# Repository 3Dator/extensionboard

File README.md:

3Dator extensionboard firmware
======

This repository contains the firmware for our tiny extensionboard that is used to drive the LEDs and both Fans.

Also there is a voltage devider for the 12V Feedback pin of the inductive z probe.

For more information visit our website or wiki:

http://3dator.com

http://wiki.3dator.com

#how to use
If you want to play arrount with the sourcecode on your board you need a ISP Programmer which is supported by Arduino IDE. (e.g. stk 500)

#License
Please note that the material in this repository is licensed with the CC BY-NC-SA

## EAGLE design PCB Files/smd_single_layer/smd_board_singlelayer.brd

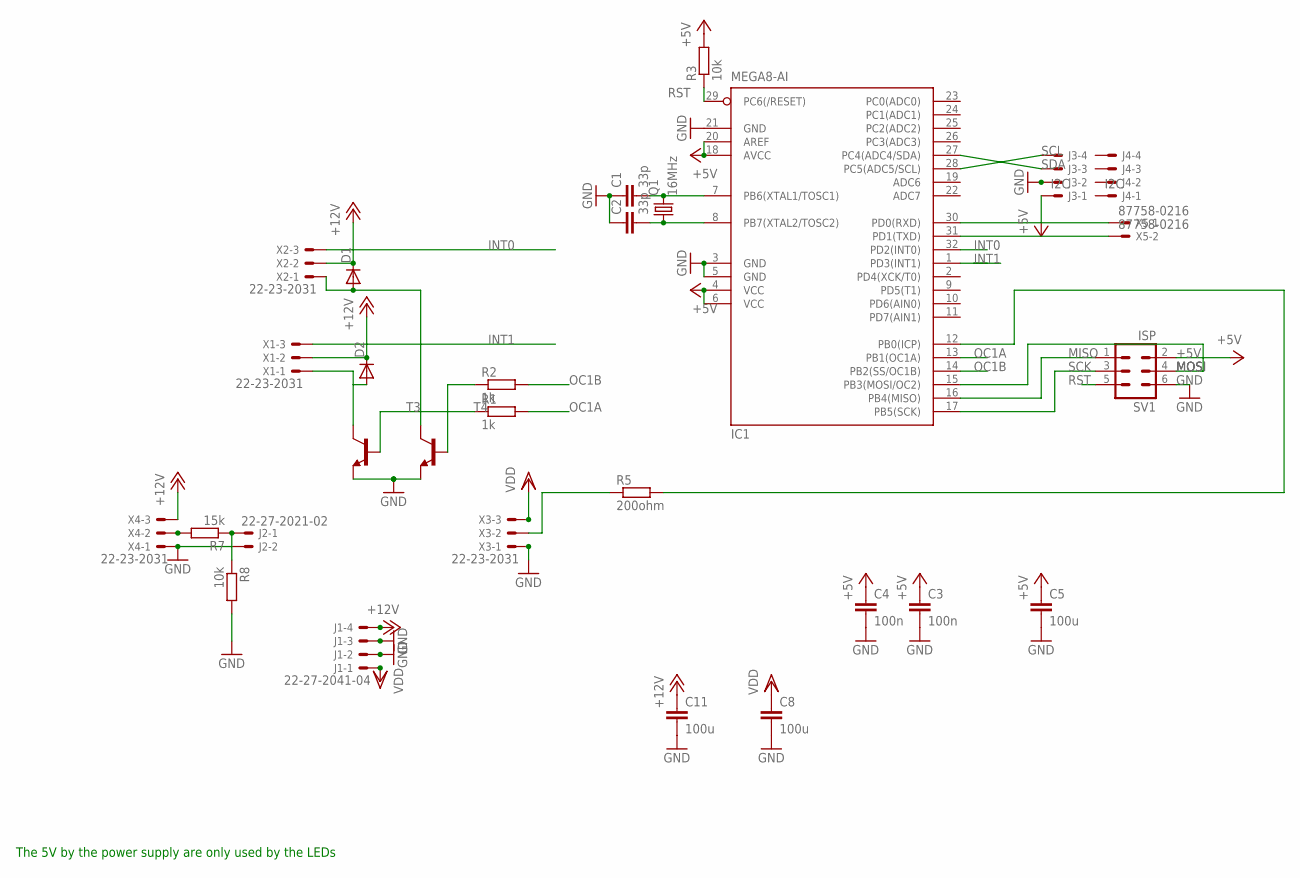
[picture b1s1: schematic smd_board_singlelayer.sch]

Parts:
C1, C2: 33p; C1206
C3, C4: 100n; C1206
C5, C8, C11: 100u; C1206
D1, D2: DIODE-SOD80C; SOD80C
IC1: MEGA8-AI; TQFP32-08
J1: 22-27-2041-04; 6410-04
J2: 22-27-2021-02; 6410-02
J3, J4: I2C; 6410-04
Q1: 16MHz; HC49UP
R1, R2: 1k; M1206
R3, R8: 10k; M1206
R5: 200ohm; M1206
R7: 15k; M1206
SV1: ISP; ML6
T3, T4: BC808-NPN-SOT23-BEC; SOT23-BEC
X1, X2, X3, X4: 22-23-2031
X5: 87758-0216

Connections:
+5V: C3.1, C4.1, C5.1, IC1.4 (VCC), IC1.6 (VCC), IC1.18 (AVCC), IC1.20 (AREF), J3.1, R3.2, SV1.2
+12V: C11.1, D1.C, D2.C, J1.4, X1.2, X2.2, X4.3
GND: C1.1, C2.1, C3.2, C4.2, C5.2, C8.2, C11.2, IC1.3 (GND), IC1.5 (GND), IC1.21 (GND), J1.2, J1.3, J2.2, J3.2, R8.2, SV1.6, T3.E, T4.E, X3.1, X4.1
INT0: IC1.32 (PD2(INT0)), X2.3
INT1: IC1.1 (PD3(INT1)), X1.3
MISO: IC1.16 (PB4(MISO)), SV1.1
MOSI: IC1.15 (PB3(MOSI/OC2)), SV1.4
unnamed: C1.2, IC1.7 (PB6(XTAL1/TOSC1)), Q1.2
unnamed: D2.A, T3.C, X1.1
unnamed: D1.A, T4.C, X2.1
unnamed: R2.1, T4.B
unnamed: R1.1, T3.B
unnamed: R5.1, X3.2
unnamed: C2.2, IC1.8 (PB7(XTAL2/TOSC2)), Q1.1
unnamed: IC1.30 (PD0(RXD)), X5.1
unnamed: R7.2, X4.2
unnamed: J2.1, R7.1, R8.1
unnamed: IC1.12 (PB0(ICP)), R5.2
unnamed: IC1.31 (PD1(TXD)), X5.2
OC1A: IC1.13 (PB1(OC1A)), R1.2
OC1B: IC1.14 (PB2(SS/OC1B)), R2.2
RST: IC1.29 (PC6(/RESET)), R3.1, SV1.5
SCK: IC1.17 (PB5(SCK)), SV1.3
SCL: IC1.28 (PC5(ADC5/SCL)), J3.4
SDA: IC1.27 (PC4(ADC4/SDA)), J3.3
VDD: C8.1, J1.1, X3.3

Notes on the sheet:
The 5V by the power supply are only used by the LEDs

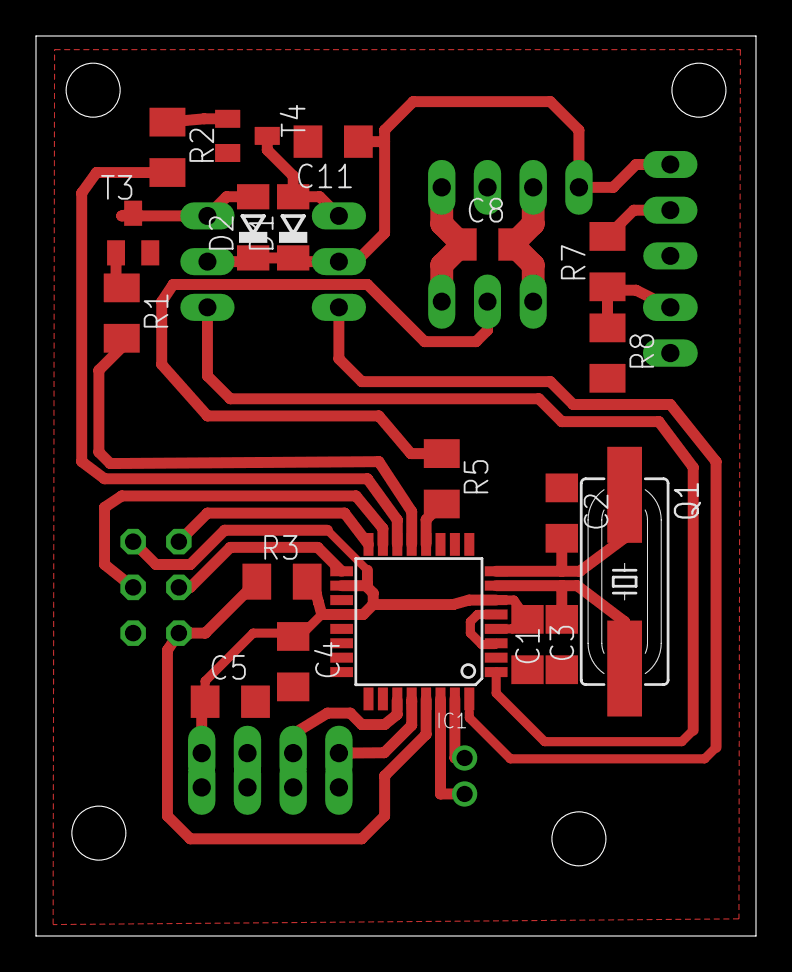
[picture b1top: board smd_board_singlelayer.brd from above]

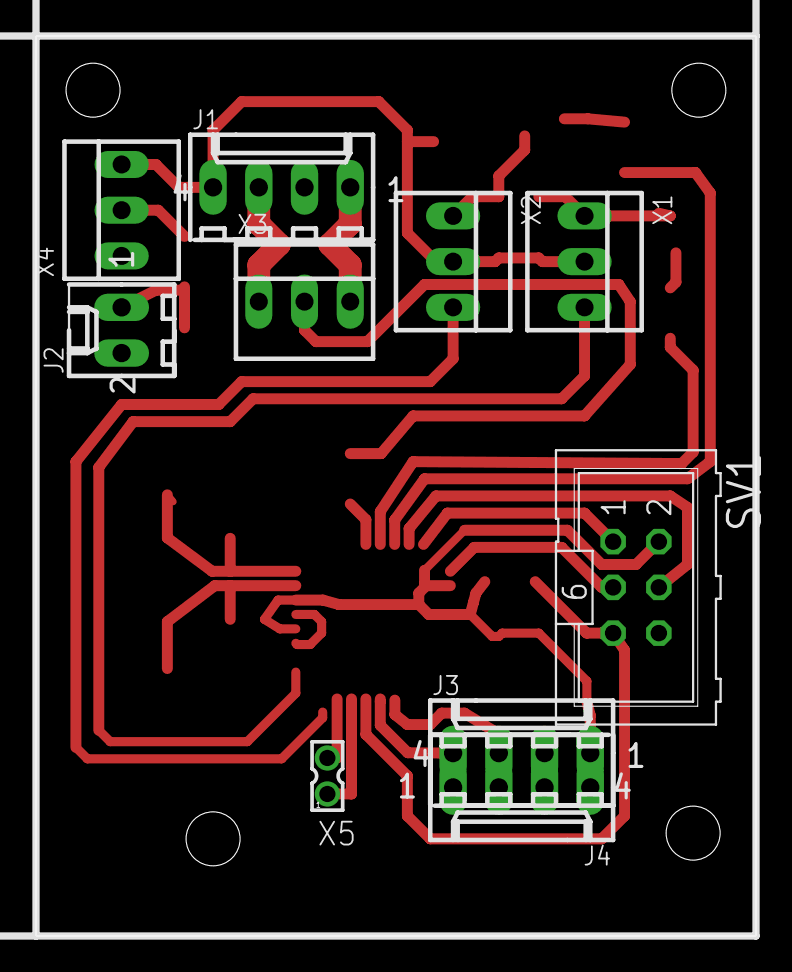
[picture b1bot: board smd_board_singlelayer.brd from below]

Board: 2 copper layers, 40.0 x 50.0 mm, 29 parts (10 on the bottom side), 26 nets.

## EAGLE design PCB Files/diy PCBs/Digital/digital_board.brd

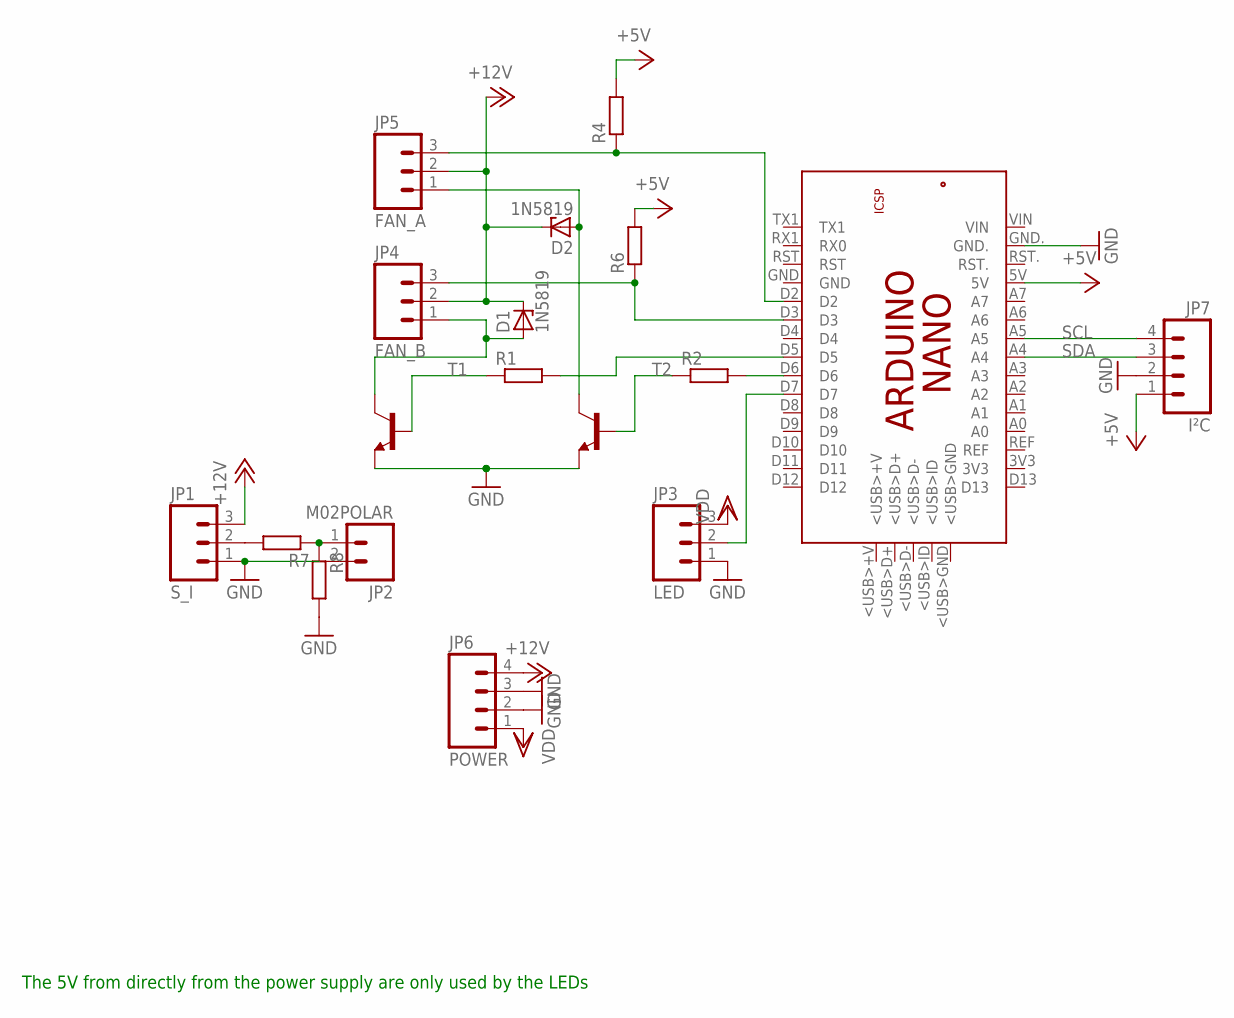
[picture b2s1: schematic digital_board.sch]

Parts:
D1, D2: 1N5819; DO35Z10
JP1: S_I; MOLEX-1X3
JP2: M02POLAR; MOLEX-1X2
JP3: LED; MOLEX-1X3
JP4: FAN_B; MOLEX-1X3
JP5: FAN_A; MOLEX-1X3
JP6: POWER; MOLEX-1X4
JP7: I²C; MOLEX-1X4
PCB2: ARDUINO_NANO
R1, R2, R4, R6, R7, R8: R-EU_0309/10; 0309/10
T1, T2: BC548-NPN-TO92-CBE; TO92-CBE

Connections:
+5V: JP7.1, PCB2.5V, R4.2, R6.2
+12V: D1.C, D2.C, JP1.3, JP4.2, JP5.2, JP6.4
GND: JP1.1, JP2.2, JP3.1, JP6.2, JP6.3, JP7.2, PCB2.GND., R8.2, T1.E, T2.E
unnamed: D1.A, JP4.1, T1.C
unnamed: D2.A, JP5.1, T2.C
unnamed: R1.1, T1.B
unnamed: PCB2.D5, R1.2
unnamed: PCB2.D6, R2.2
unnamed: JP4.3, PCB2.D3, R6.1
unnamed: JP5.3, PCB2.D2, R4.1
unnamed: JP1.2, R7.2
unnamed: JP2.1, R7.1, R8.1
unnamed: JP3.2, PCB2.D7
SCL: JP7.4, PCB2.A5
SDA: JP7.3, PCB2.A4
VDD: JP3.3, JP6.1

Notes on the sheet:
The 5V from directly from the power supply are only used by the LEDs

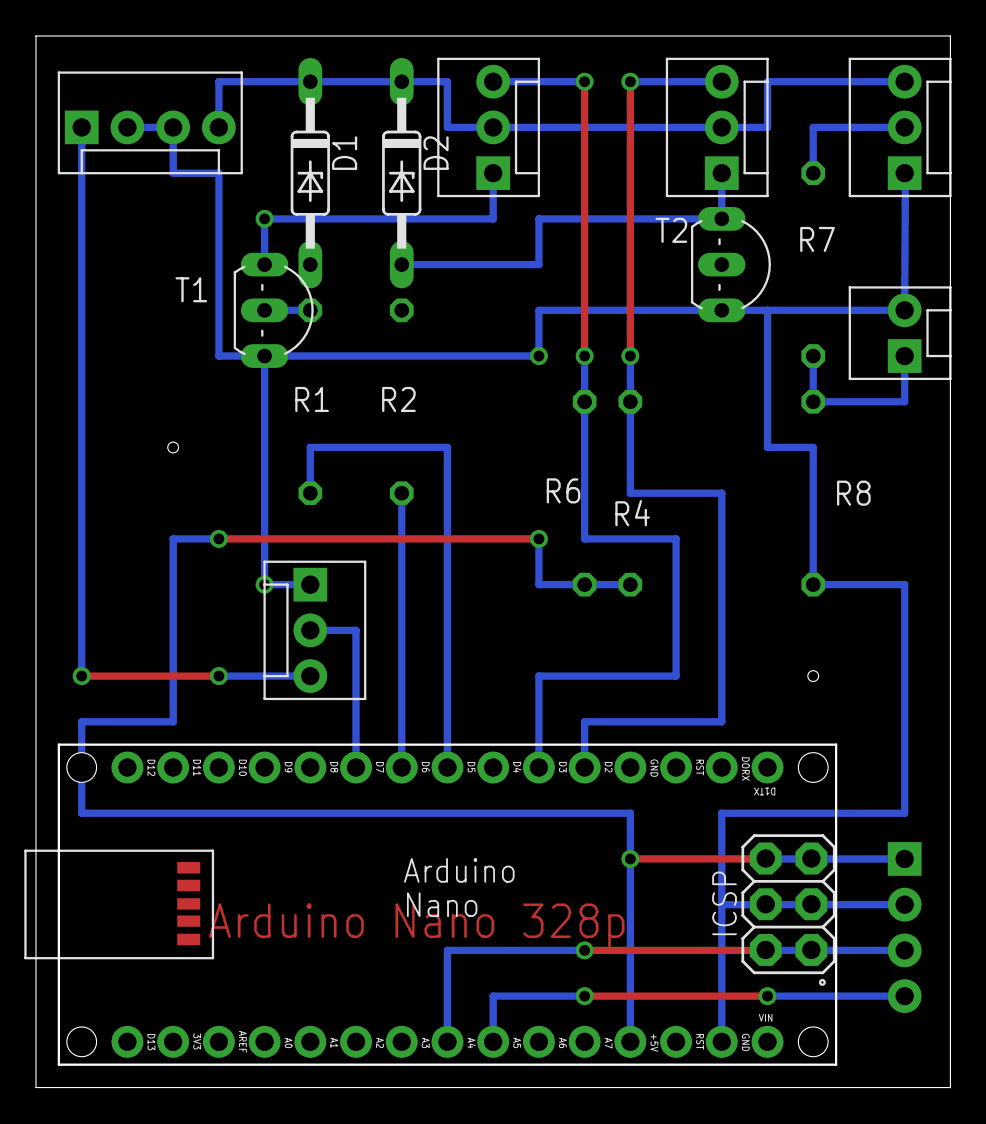
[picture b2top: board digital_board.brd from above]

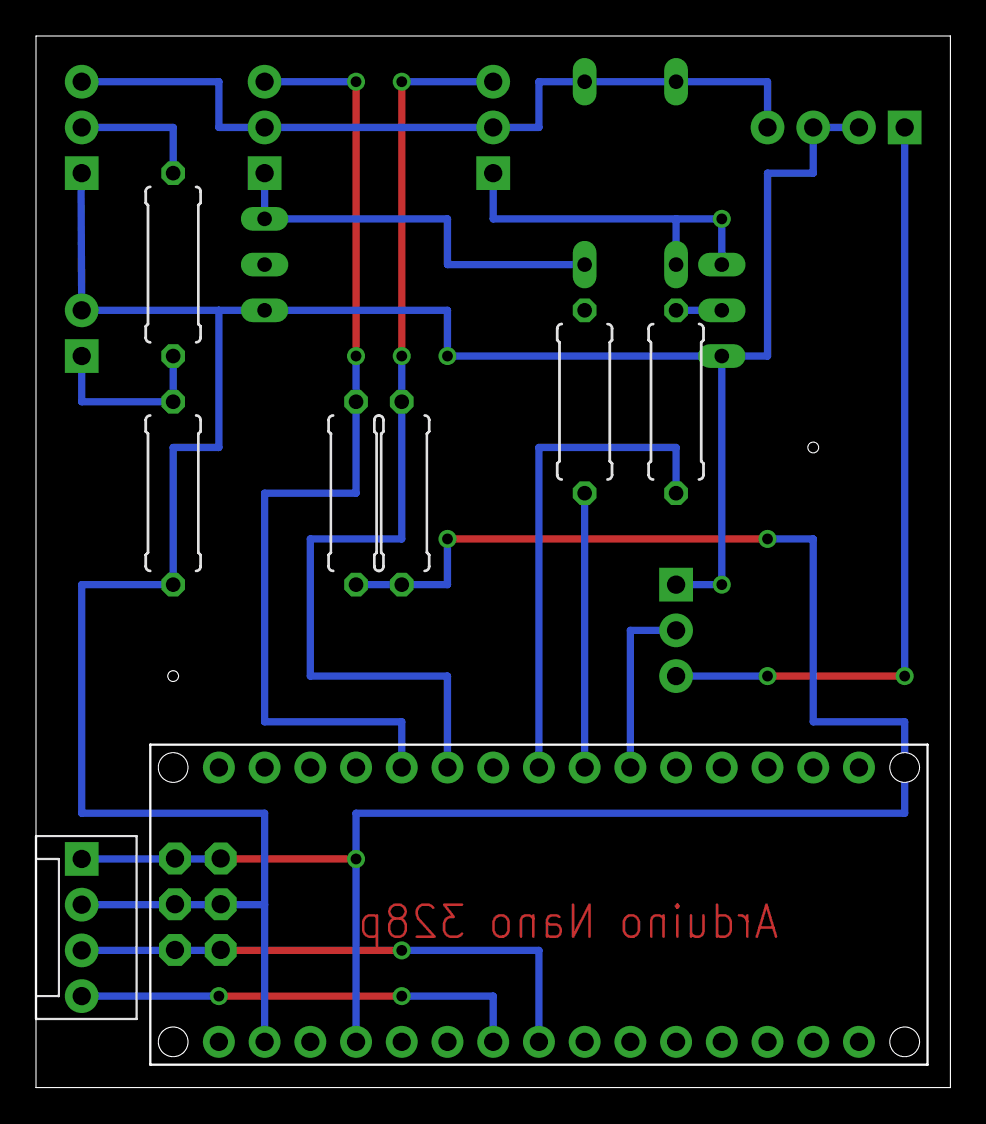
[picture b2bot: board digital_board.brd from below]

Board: 2 copper layers, 50.8 x 58.4 mm, 18 parts (7 on the bottom side), 16 nets.

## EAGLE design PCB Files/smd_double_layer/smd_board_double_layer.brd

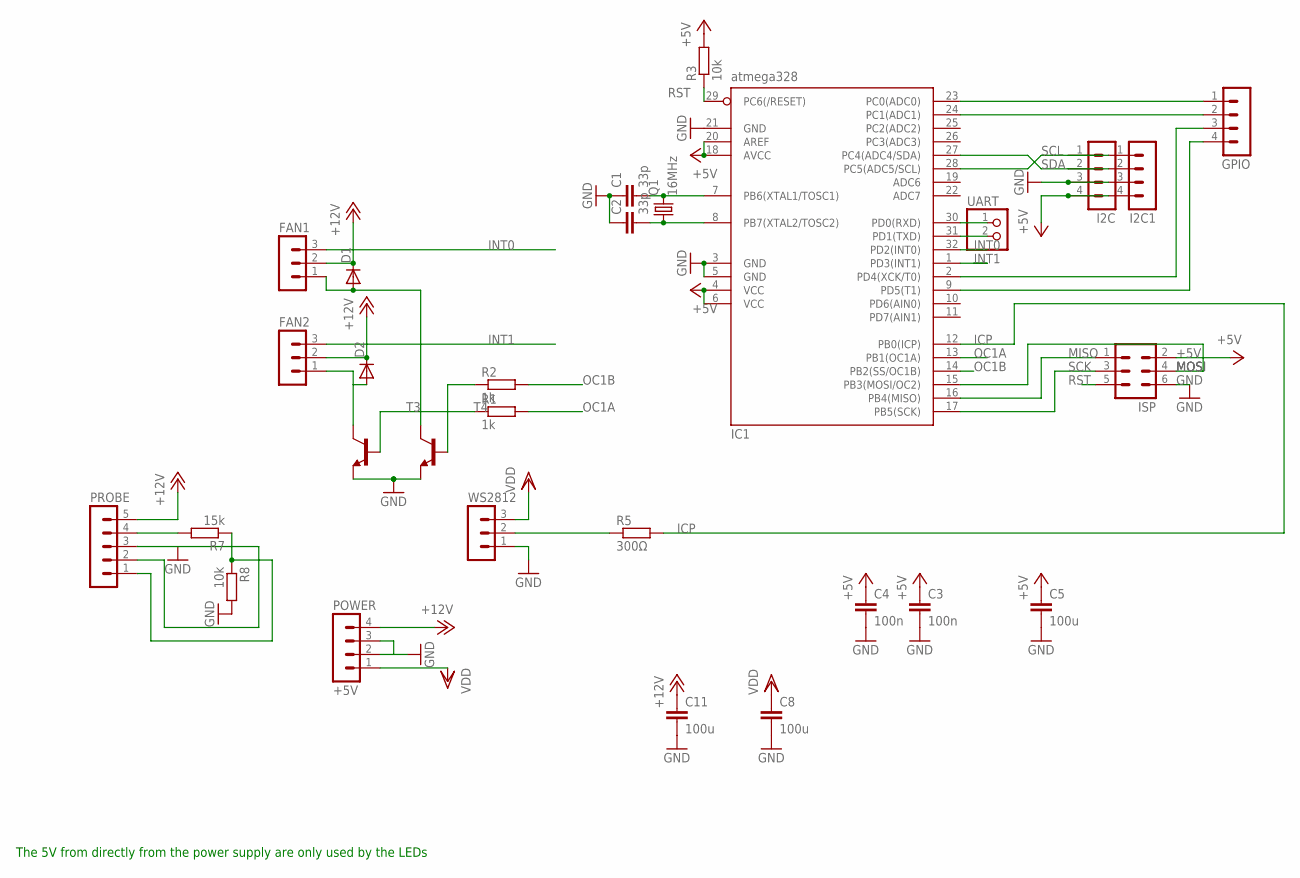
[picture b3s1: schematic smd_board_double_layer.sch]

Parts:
C1, C2: 33p; C1206
C3, C4: 100n; C1206
C5, C8, C11: 100u; C1206
D1, D2: DIODE-SOD80C; SOD80C
FAN1, FAN2: MA03-1
GPIO: MA04-1
I2C, I2C1: MA04-1
IC1: atmega328; TQFP32-08
ISP: MA03-2
POWER: +5V; MA04-1
PROBE: MA05-1
Q1: 16MHz; HC49UP
R1: 1k; M1206
R2: 1k; R1206
R3, R8: 10k; M1206
R5: 300Ω; R1206
R7: 15k; M1206
T3, T4: BC808-NPN-SOT23-BEC; SOT23-BEC
UART: PINHD-1X2; 1X02
WS2812: MA03-1

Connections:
+5V: C3.1, C4.1, C5.1, I2C.4, I2C1.4, IC1.4 (VCC), IC1.6 (VCC), IC1.18 (AVCC), IC1.20 (AREF), ISP.2, R3.2
+12V: C11.1, D1.C, D2.C, FAN1.2, FAN2.2, POWER.4, PROBE.5
GND: C1.1, C2.1, C3.2, C4.2, C5.2, C8.2, C11.2, I2C.3, I2C1.3, IC1.3 (GND), IC1.5 (GND), IC1.21 (GND), ISP.6, POWER.2, POWER.3, PROBE.2, PROBE.3, R8.2, T3.E, T4.E, WS2812.1
ICP: IC1.12 (PB0(ICP)), R5.2
INT0: FAN1.3, IC1.32 (PD2(INT0))
INT1: FAN2.3, IC1.1 (PD3(INT1))
MISO: IC1.16 (PB4(MISO)), ISP.1
MOSI: IC1.15 (PB3(MOSI/OC2)), ISP.4
unnamed: C1.2, IC1.7 (PB6(XTAL1/TOSC1)), Q1.2
unnamed: D2.A, FAN2.1, T3.C
unnamed: D1.A, FAN1.1, T4.C
unnamed: R2.1, T4.B
unnamed: R1.1, T3.B
unnamed: R5.1, WS2812.2
unnamed: C2.2, IC1.8 (PB7(XTAL2/TOSC2)), Q1.1
unnamed: IC1.30 (PD0(RXD)), UART.1
unnamed: PROBE.4, R7.2
unnamed: GPIO.1, IC1.23 (PC0(ADC0))
unnamed: GPIO.2, IC1.24 (PC1(ADC1))
unnamed: IC1.31 (PD1(TXD)), UART.2
unnamed: GPIO.4, IC1.9 (PD5(T1))
unnamed: PROBE.1, R7.1, R8.1
unnamed: GPIO.3, IC1.2 (PD4(XCK/T0))
OC1A: IC1.13 (PB1(OC1A)), R1.2
OC1B: IC1.14 (PB2(SS/OC1B)), R2.2
RST: IC1.29 (PC6(/RESET)), ISP.5, R3.1
SCK: IC1.17 (PB5(SCK)), ISP.3
SCL: I2C.1, I2C1.1, IC1.28 (PC5(ADC5/SCL))
SDA: I2C.2, I2C1.2, IC1.27 (PC4(ADC4/SDA))
VDD: C8.1, POWER.1, WS2812.3

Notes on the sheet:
The 5V from directly from the power supply are only used by the LEDs

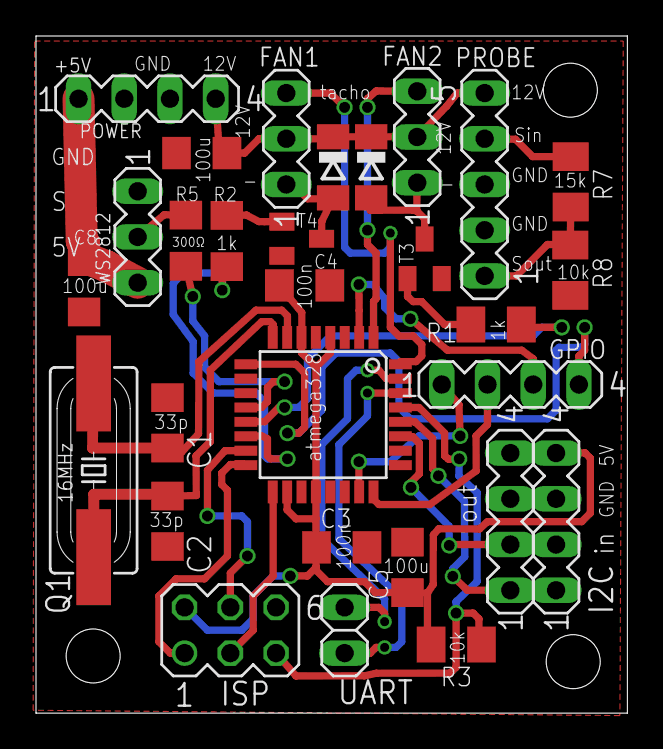
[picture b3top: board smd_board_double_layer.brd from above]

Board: 2 copper layers, 32.9 x 37.6 mm, 29 parts (0 on the bottom side), 30 nets.

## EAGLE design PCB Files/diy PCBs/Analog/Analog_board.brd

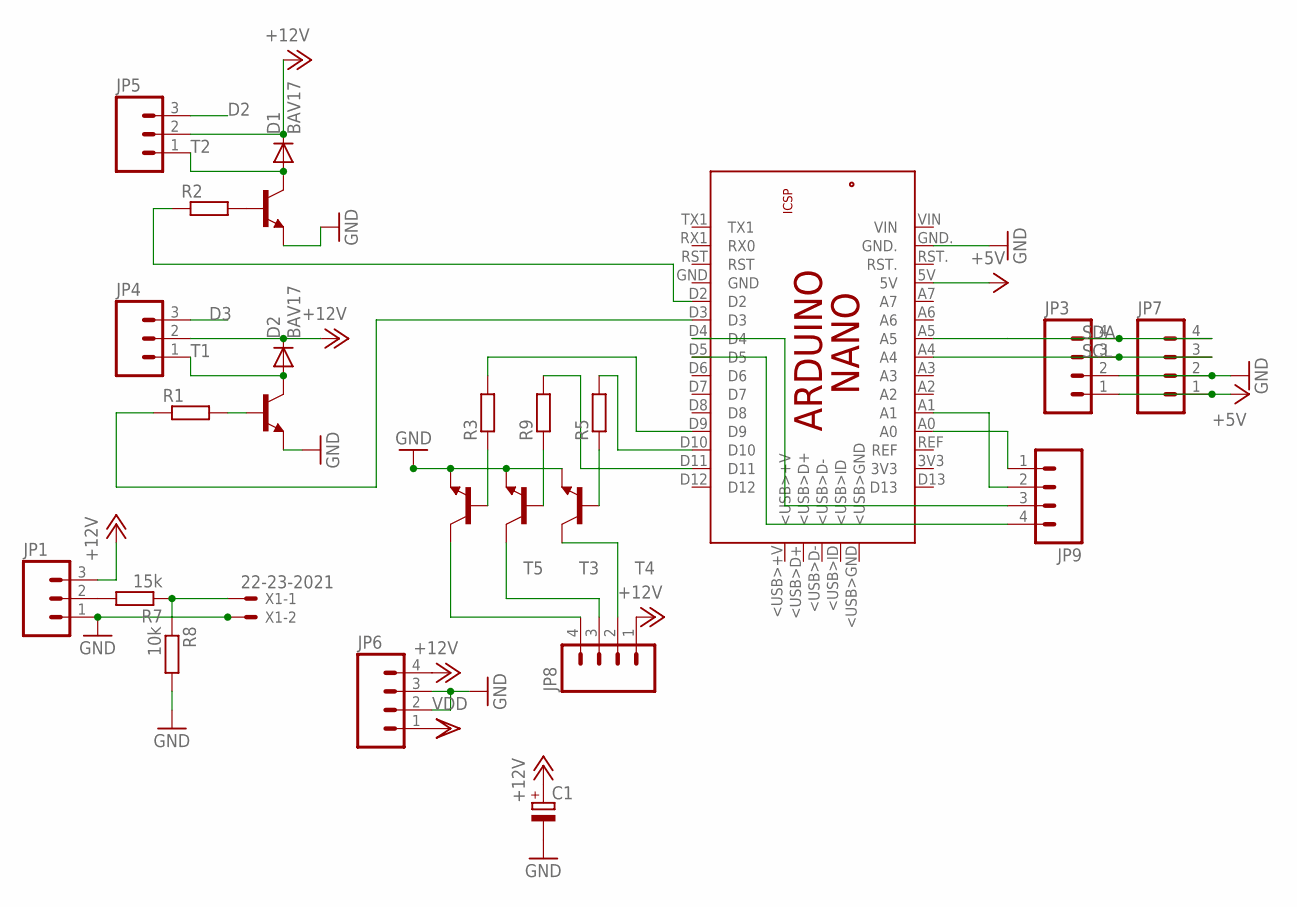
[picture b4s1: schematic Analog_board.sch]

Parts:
C1: CPOL-EUE3.5-10; E3,5-10
D1, D2: BAV17; DO35-10
JP1, JP4, JP5: M03POLAR; MOLEX-1X3
JP3, JP6, JP7, JP8, JP9: M04POLAR; MOLEX-1X4
PCB2: ARDUINO_NANO
R1: R-EU_0309/12; 0309/12
R2, R3, R5, R9: R-EU_0309/10; 0309/10
R7: 15k; 0309/10
R8: 10k; 0309/10
T1, T2, T3, T4, T5: BC548-NPN-TO92-CBE; TO92-CBE
X1: 22-23-2021

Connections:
+5V: JP3.1, JP7.1, PCB2.5V
+12V: C1.+, D1.C, D2.C, JP1.3, JP4.2, JP5.2, JP6.4, JP8.1
D2: JP5.3
D3: JP4.3
D4: PCB2.D2, R2.1
D5: PCB2.D3, R1.1
GND: C1.-, JP1.1, JP3.2, JP6.2, JP6.3, JP7.2, PCB2.GND., R8.2, T1.E, T2.E, T3.E, T4.E, T5.E, X1.2
unnamed: JP8.4, T5.C
unnamed: R3.1, T5.B
unnamed: D2.A, JP4.1, T1.C
unnamed: D1.A, JP5.1, T2.C
unnamed: R1.2, T1.B
unnamed: R2.2, T2.B
unnamed: JP9.1, PCB2.A0
unnamed: JP9.2, PCB2.A1
unnamed: R5.1, T4.B
unnamed: PCB2.D9, R3.2
unnamed: R9.1, T3.B
unnamed: JP9.3, PCB2.D4
unnamed: JP9.4, PCB2.D5
unnamed: JP1.2, R7.2
unnamed: R7.1, R8.1, X1.1
unnamed: PCB2.D10, R5.2
unnamed: PCB2.D11, R9.2
unnamed: JP8.3, T3.C
unnamed: JP8.2, T4.C
SCL: JP3.4, JP7.4, PCB2.A5
SDA: JP3.3, JP7.3, PCB2.A4
VDD: JP6.1

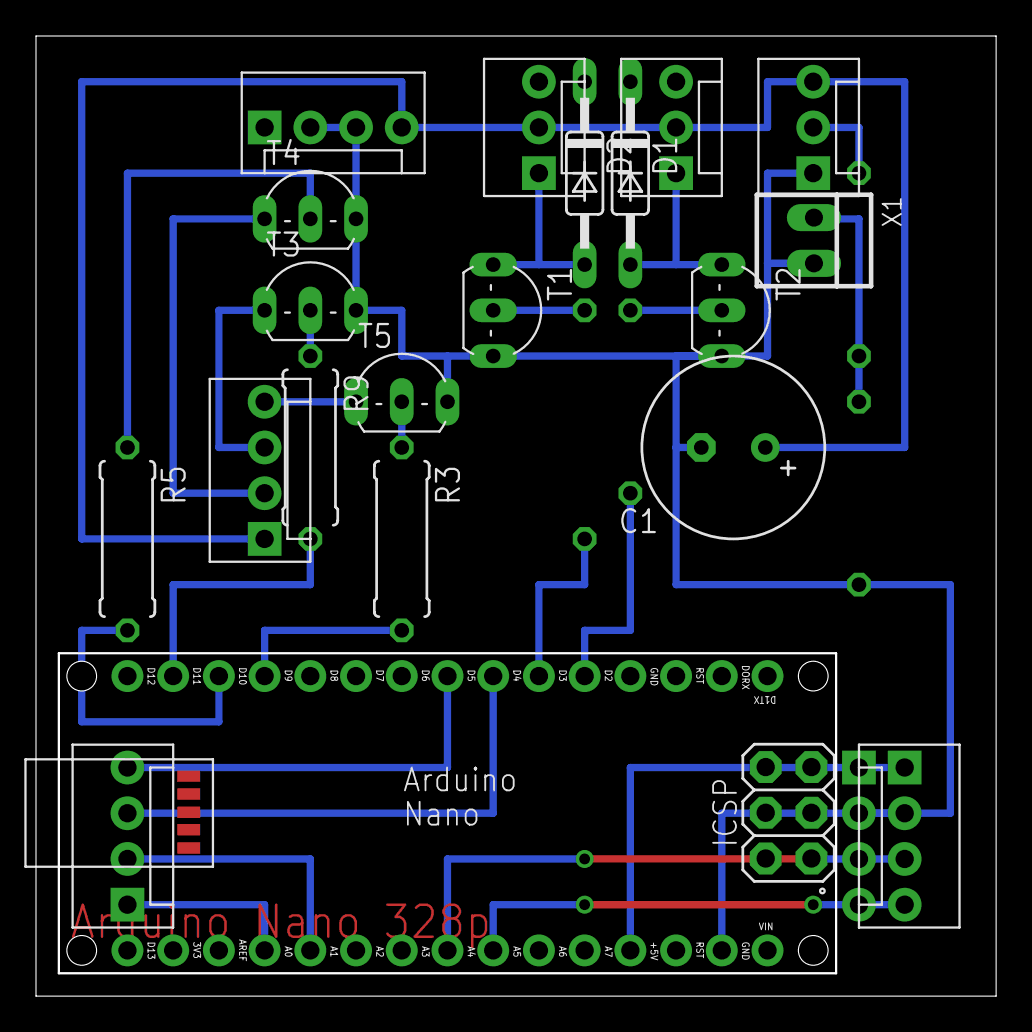
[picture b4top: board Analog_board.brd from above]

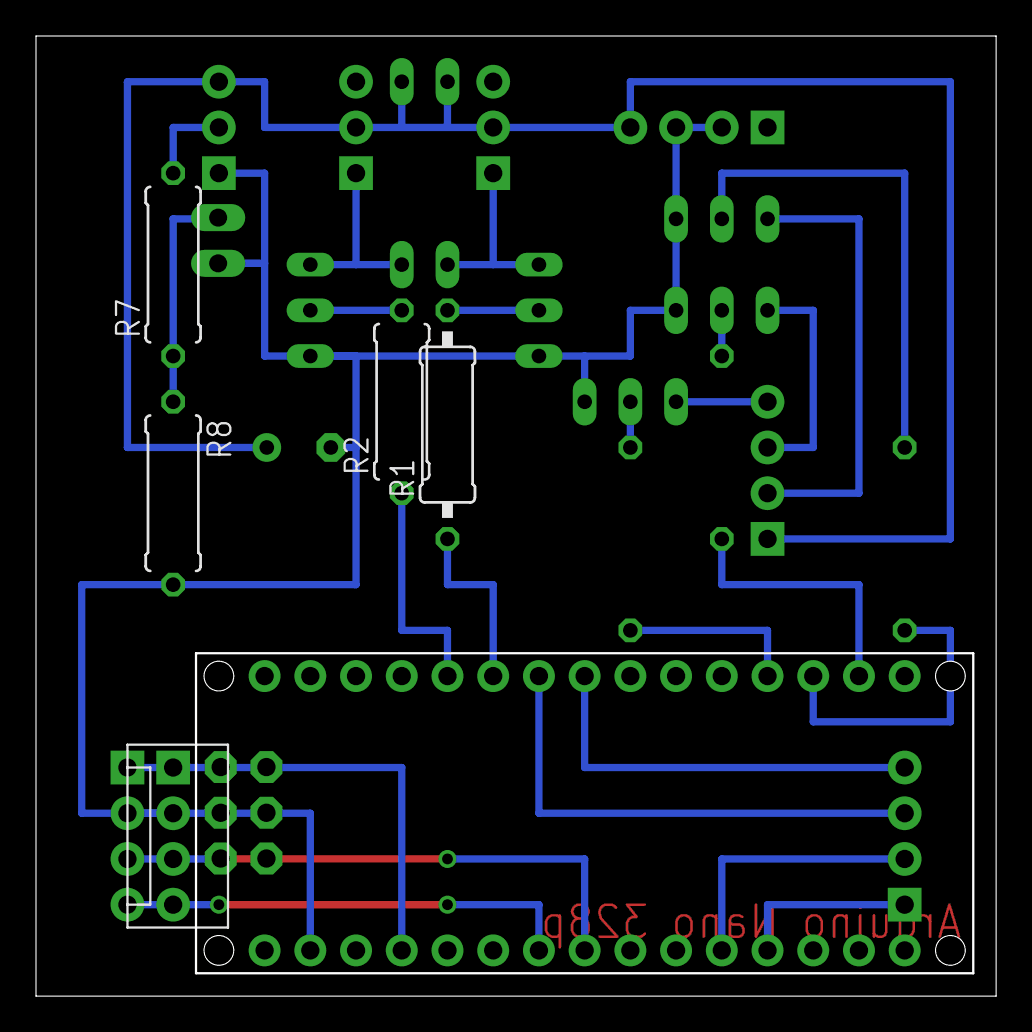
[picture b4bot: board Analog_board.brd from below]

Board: 2 copper layers, 53.3 x 53.3 mm, 25 parts (5 on the bottom side), 26 nets.

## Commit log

2015-10-09 command registration finished
2015-11-04 cleaned working directory
2015-11-04 adding gitignore
2015-12-27 uploaded new source code
2016-01-05 updated pixel value
2016-01-07 using real pwm
2016-01-07 added more defines
2016-01-08 fixed fade function
2016-01-08 little refactoring
2016-01-09 major redesign
2016-01-09 adde jitter mode
2016-01-10 added test programms
2016-01-10 added overwrite for every led
2016-01-13 added pulse and rainbow toggle
2016-01-13 fixed bad english
2016-01-26 fixed fan issue
2016-01-28 made looping programms overwrite each other, added end looping programm, added loop x times
2016-01-28 added programm 11 to set brightness
2016-08-05 added code for analog board (untested)
2016-08-27 made analog extensionboard firmware working
2016-08-27 fixed rainbow on analog board
2017-07-10 added PCB files for the Extension Board
    There is a PCB file for DIY PCBs for both Analog and Digital LED Stripes
2017-07-10 made fixed a small bug and changed diode parameters
2017-07-10 updated files

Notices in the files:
parts and their libraries:
SparkFun-Connectors: Licensing: Creative Commons ShareAlike 4.0 International - https://creativecommons.org/licenses/by-sa/4.0
